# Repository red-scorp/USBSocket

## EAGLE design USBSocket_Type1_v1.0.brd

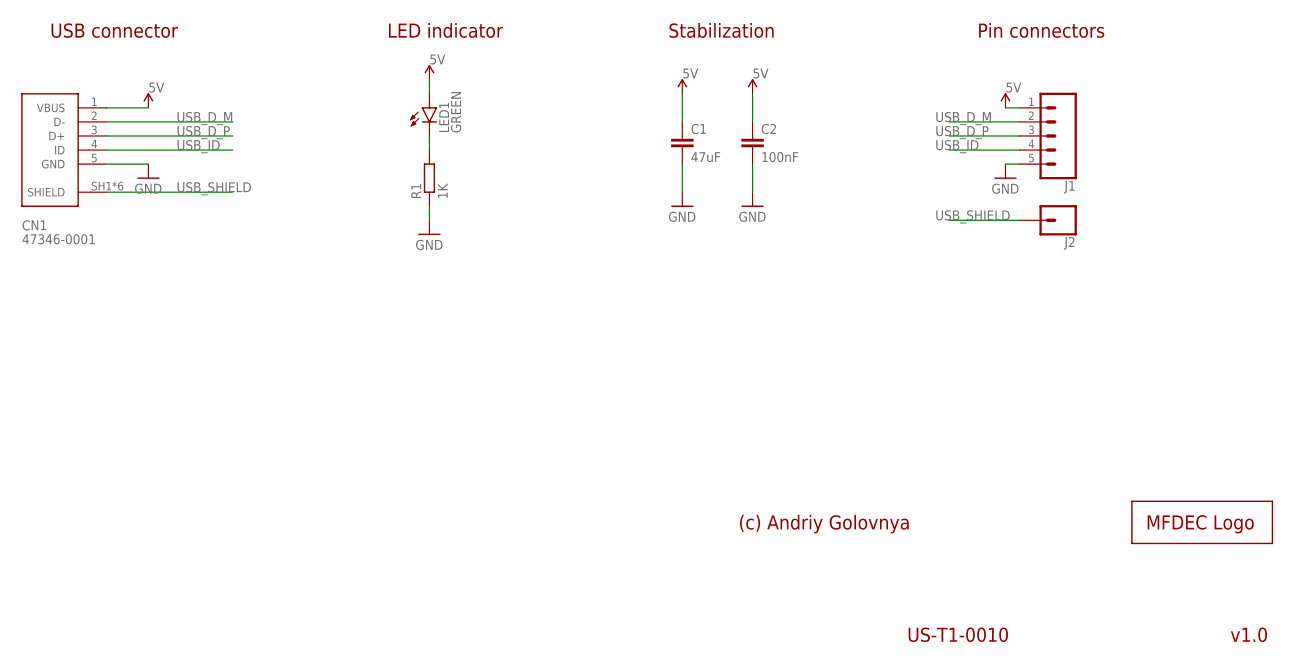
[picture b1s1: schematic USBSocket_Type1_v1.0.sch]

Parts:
C1: 47uF; C0805
C2: 100nF; C0402
CN1: 47346-0001; MOLEX_47346-0001
J1: CONN_05PTH; 1X05
J2: CONN_01; 1X01
LED1: GREEN; SML0603
LOGO1: MFDECLOGO_L_10MM; MFDEC_L_10MM
R1: 1K; R0402

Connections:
5V: C1.1, C2.1, CN1.1 (VBUS), J1.1, LED1.A
GND: C1.2, C2.2, CN1.5 (GND), J1.5, R1.1
unnamed: LED1.C, R1.2
USB_D_M: CN1.2 (D-), J1.2
USB_D_P: CN1.3 (D+), J1.3
USB_ID: CN1.4 (ID), J1.4
USB_SHIELD: CN1.SH1 (SHIELD), CN1.SH2 (SHIELD), CN1.SH3 (SHIELD), CN1.SH4 (SHIELD), CN1.SH5 (SHIELD), CN1.SH6 (SHIELD), J2.1

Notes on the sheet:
USB connector
v1.0
LED indicator
(c) Andriy Golovnya
US-T1-0010
Stabilization
Pin connectors

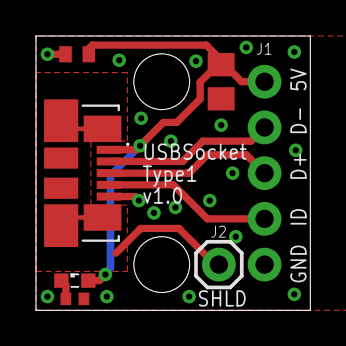
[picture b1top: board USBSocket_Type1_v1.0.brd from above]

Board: 2 copper layers, 15.2 x 15.2 mm, 8 parts (1 on the bottom side), 7 nets.

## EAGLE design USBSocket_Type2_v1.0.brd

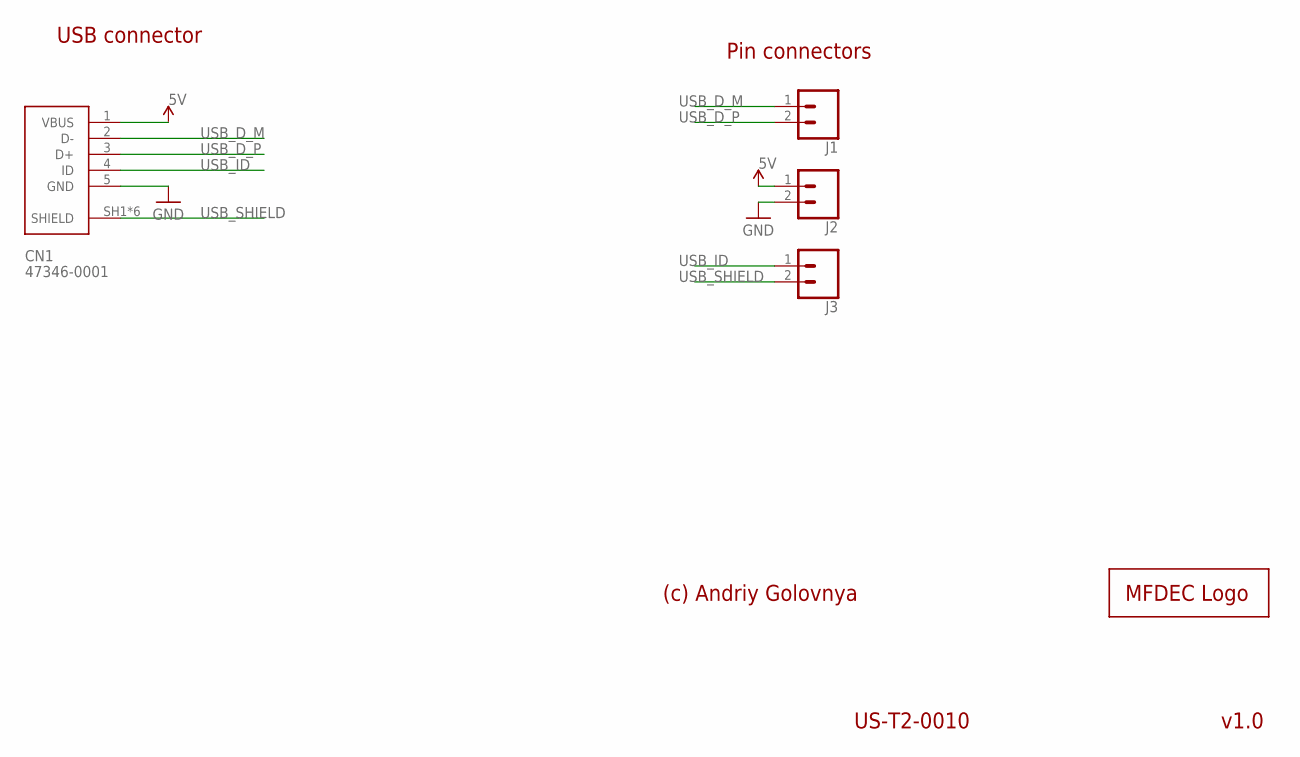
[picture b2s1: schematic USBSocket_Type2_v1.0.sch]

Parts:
CN1: 47346-0001; MOLEX_47346-0001
J1, J2, J3: CONN_02; 1X02
LOGO1: MFDECLOGO_L_10MM; MFDEC_L_10MM

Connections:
5V: CN1.1 (VBUS), J2.1
GND: CN1.5 (GND), J2.2
USB_D_M: CN1.2 (D-), J1.1
USB_D_P: CN1.3 (D+), J1.2
USB_ID: CN1.4 (ID), J3.1
USB_SHIELD: CN1.SH1 (SHIELD), CN1.SH2 (SHIELD), CN1.SH3 (SHIELD), CN1.SH4 (SHIELD), CN1.SH5 (SHIELD), CN1.SH6 (SHIELD), J3.2

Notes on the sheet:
USB connector
v1.0
(c) Andriy Golovnya
US-T2-0010
Pin connectors

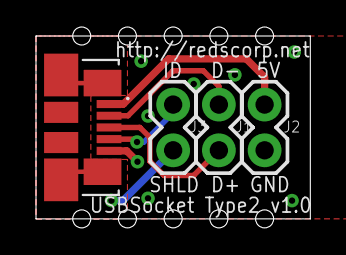
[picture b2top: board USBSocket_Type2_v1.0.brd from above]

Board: 2 copper layers, 15.2 x 10.2 mm, 5 parts (1 on the bottom side), 6 nets.

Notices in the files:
parts and their libraries:
SparkFun-Connectors: Licensing: Creative Commons ShareAlike 4.0 International - https://creativecommons.org/licenses/by-sa/4.0
